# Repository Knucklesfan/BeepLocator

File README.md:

# BeepLocator
~$5 BLE Locator with Android App

## What is this?

This is a roughly $5-$10 BLE Beacon/Keys locator that is open source, easy to build and most importantly; Fun!

## Status

This project is still heavily in development.

### v1 Motherboard design
V1 had a design flaw in that you really can't easily solder onto the battery pad on the back. A bodge wire to override battery support, and it works! ...kinda.
|  |    |
|-------------------------------------------------------------------------------------------------|-------------------------------------------------------------------------------------------|
|      |  |

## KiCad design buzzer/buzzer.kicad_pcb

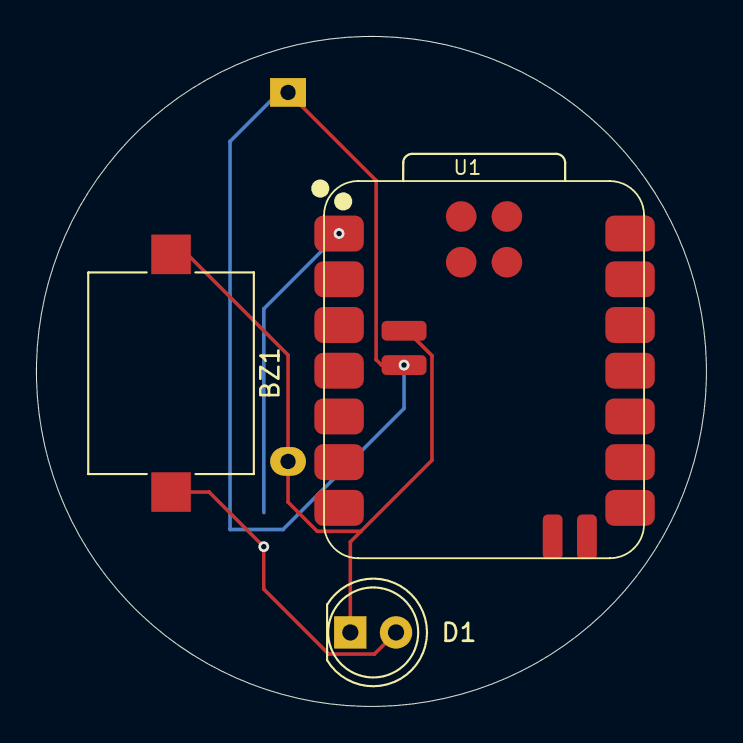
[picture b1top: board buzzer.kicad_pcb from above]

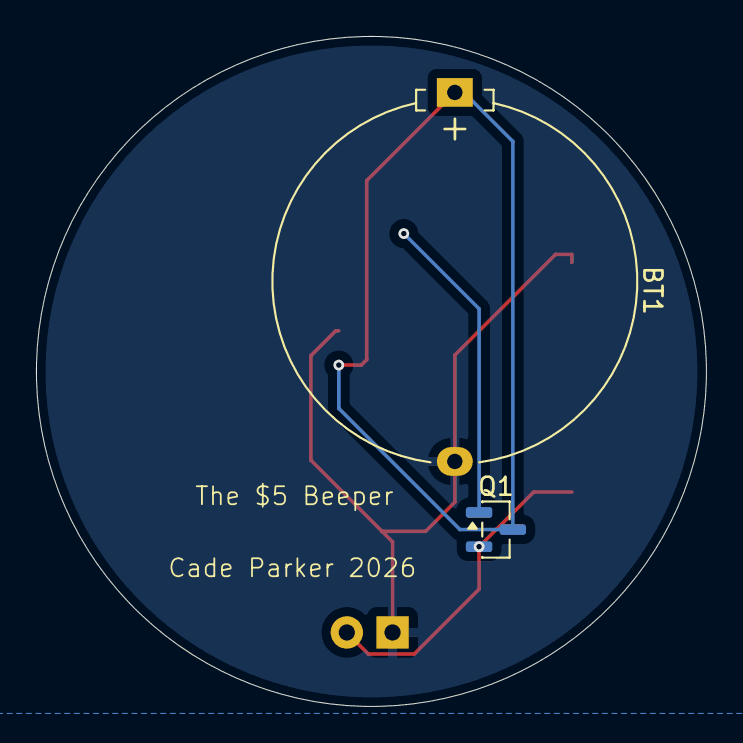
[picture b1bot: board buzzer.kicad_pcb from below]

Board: 2 copper layers, 37.2 x 37.2 mm, 5 parts (2 on the bottom side), 4 nets.

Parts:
BT1: Battery_Cell; Battery_Panasonic_CR2032-HFN_Horizontal_CircularHoles
BZ1: Buzzer; Buzzer_Mallory_AST1109MLTRQ
D1: LED; LED_D5.0mm
Q1: SS8050; SOT-23
U1: XIAO-nRF52840-SMD

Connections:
GND: BT1.2 (-), BZ1.2 (-), D1.1 (K), U1.16
unnamed: BT1.1 (+), Q1.3 (C), U1.15
unnamed: BZ1.1 (+), D1.2 (A), Q1.2 (E)
unnamed: Q1.1 (B), U1.1 (P0.02_A0_D0)

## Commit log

2026-03-02 added the beeping firmware
2026-03-04 added PCB
2026-04-02 added v1 progress
